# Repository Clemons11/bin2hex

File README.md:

# bin2hex
# Version 01 of the board

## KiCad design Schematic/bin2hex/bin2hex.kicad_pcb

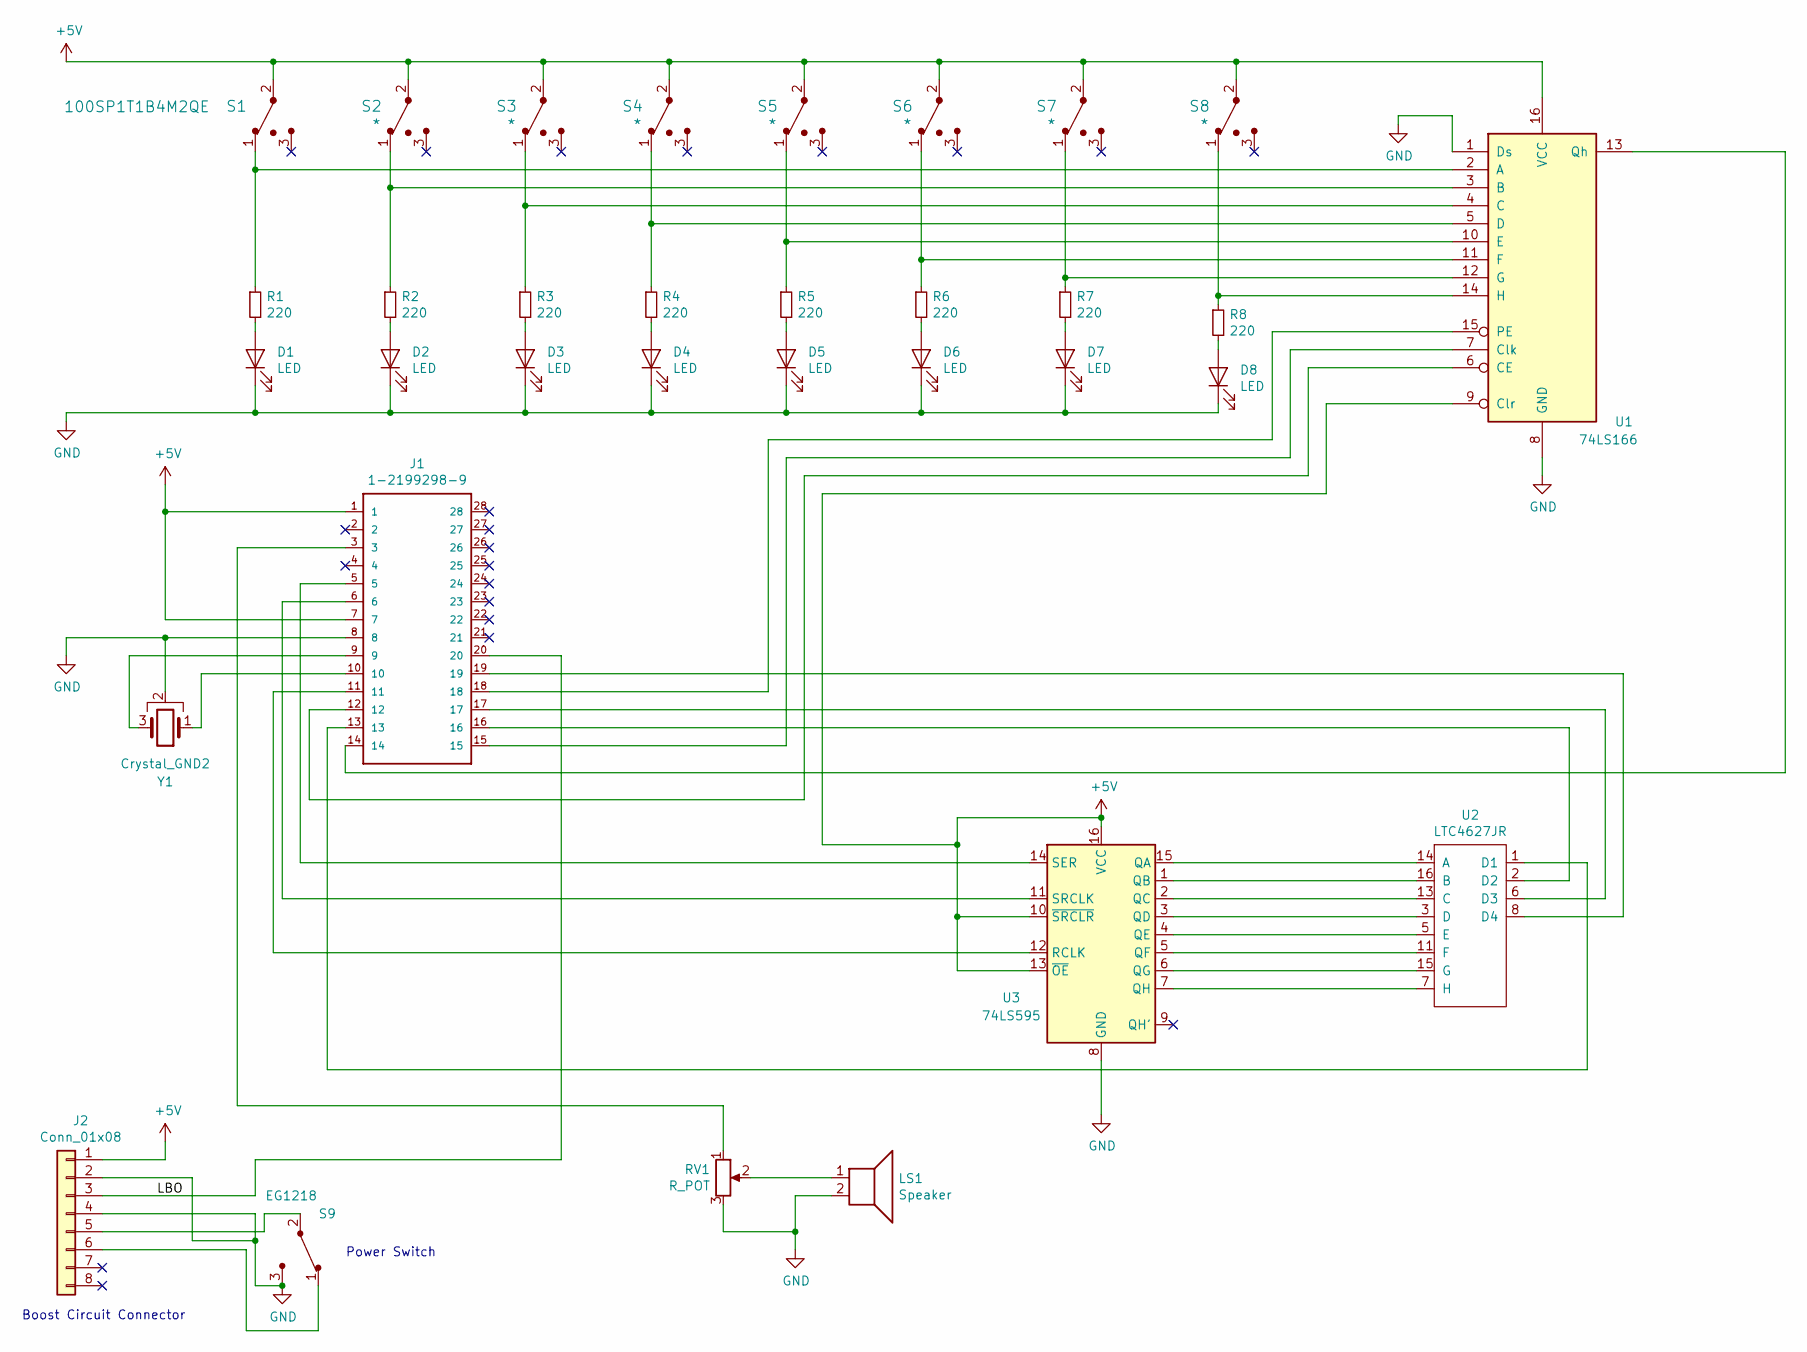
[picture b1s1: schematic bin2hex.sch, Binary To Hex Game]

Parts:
D1, D2, D3, D4, D5, D6, D7, D8: LED; TLUR4400
J1: 1-2199298-9; DIPS762W51P254L3550H419Q28N
J2: Conn_01x08; PinHeader_1x08_P2.54mm_Vertical
LS1: Speaker; SolderPad_1x2
R1, R2, R3, R4, R5, R6, R7, R8: 220; R_Axial_DIN0207_L6.3mm_D2.5mm_P7.62mm_Horizontal
RV1: R_POT; solderPads_1x3
S1: 100SP1T1B4M2QE; Toggle_Switch_100SP1T1B4M2QE; MPN 100SP1T1B4M2QE; Digi-Key_PN EG2355-ND
S2, S3, S4, S5, S6, S7, S8: *; Toggle_Switch_100SP1T1B4M2QE; MPN 100SP1T1B4M2QE; Digi-Key_PN EG2355-ND
S9: EG1218; Switch_Slide_11.6x4mm_EG1218; MPN EG1218; Digi-Key_PN EG1903-ND
U1: 74LS166; DIP254P762X508-16
U2: LTC4627JR
U3: 74LS595; DIP254P762X508-16
Y1: Crystal_GND2; XTAL_ZTT-16.00MX

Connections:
+5V: J1.1, J1.7, J2.1, S1.2 (Com), S2.2 (Com), S3.2 (Com), S4.2 (Com), S5.2 (Com), S6.2 (Com), S7.2 (Com), S8.2 (Com), U1.9 (Clr), U1.16 (VCC), U3.10 (~SRCLR), U3.13 (~OE), U3.16 (VCC)
/LBO: J1.20, J2.3
GND: D1.1 (K), D2.1 (K), D3.1 (K), D4.1 (K), D5.1 (K), D6.1 (K), D7.1 (K), D8.1 (K), J1.8, J2.2, J2.4, LS1.2, RV1.3, S9.3, U1.1 (Ds), U1.8 (GND), U3.8 (GND), Y1.2
unnamed: D1.2 (A), R1.2
unnamed: D2.2 (A), R2.2
unnamed: D3.2 (A), R3.2
unnamed: D4.2 (A), R4.2
unnamed: D5.2 (A), R5.2
unnamed: D6.2 (A), R6.2
unnamed: D7.2 (A), R7.2
unnamed: D8.2 (A), R8.2
unnamed: J1.3, RV1.1
unnamed: J1.5, U3.14 (SER)
unnamed: J1.6, U3.11 (SRCLK)
unnamed: J1.9, Y1.3
unnamed: J1.10, Y1.1
unnamed: J1.11, U3.12 (RCLK)
unnamed: J1.12, U1.6 (CE)
unnamed: J1.13, U2.1 (D1)
unnamed: J1.14, U1.13 (Qh)
unnamed: J1.15, U1.7 (Clk)
unnamed: J1.16, U2.2 (D2)
unnamed: J1.17, U2.6 (D3)
unnamed: J1.18, U1.15 (PE)
unnamed: J1.19, U2.8 (D4)
unnamed: J2.5, S9.2
unnamed: J2.6, S9.1
unnamed: LS1.1, RV1.2
unnamed: R1.1, S1.1, U1.2 (A)
unnamed: R2.1, S2.1, U1.3 (B)
unnamed: R3.1, S3.1, U1.4 (C)
unnamed: R4.1, S4.1, U1.5 (D)
unnamed: R5.1, S5.1, U1.10 (E)
unnamed: R6.1, S6.1, U1.11 (F)
unnamed: R7.1, S7.1, U1.12 (G)
unnamed: R8.1, S8.1, U1.14 (H)
unnamed: U2.3 (D), U3.3 (QD)
unnamed: U2.5 (E), U3.4 (QE)
unnamed: U2.7 (H), U3.7 (QH)
unnamed: U2.11 (F), U3.5 (QF)
unnamed: U2.13 (C), U3.2 (QC)
unnamed: U2.14 (A), U3.15 (QA)
unnamed: U2.15 (G), U3.6 (QG)
unnamed: U2.16 (B), U3.1 (QB)

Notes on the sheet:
Boost Circuit Connector
Power Switch

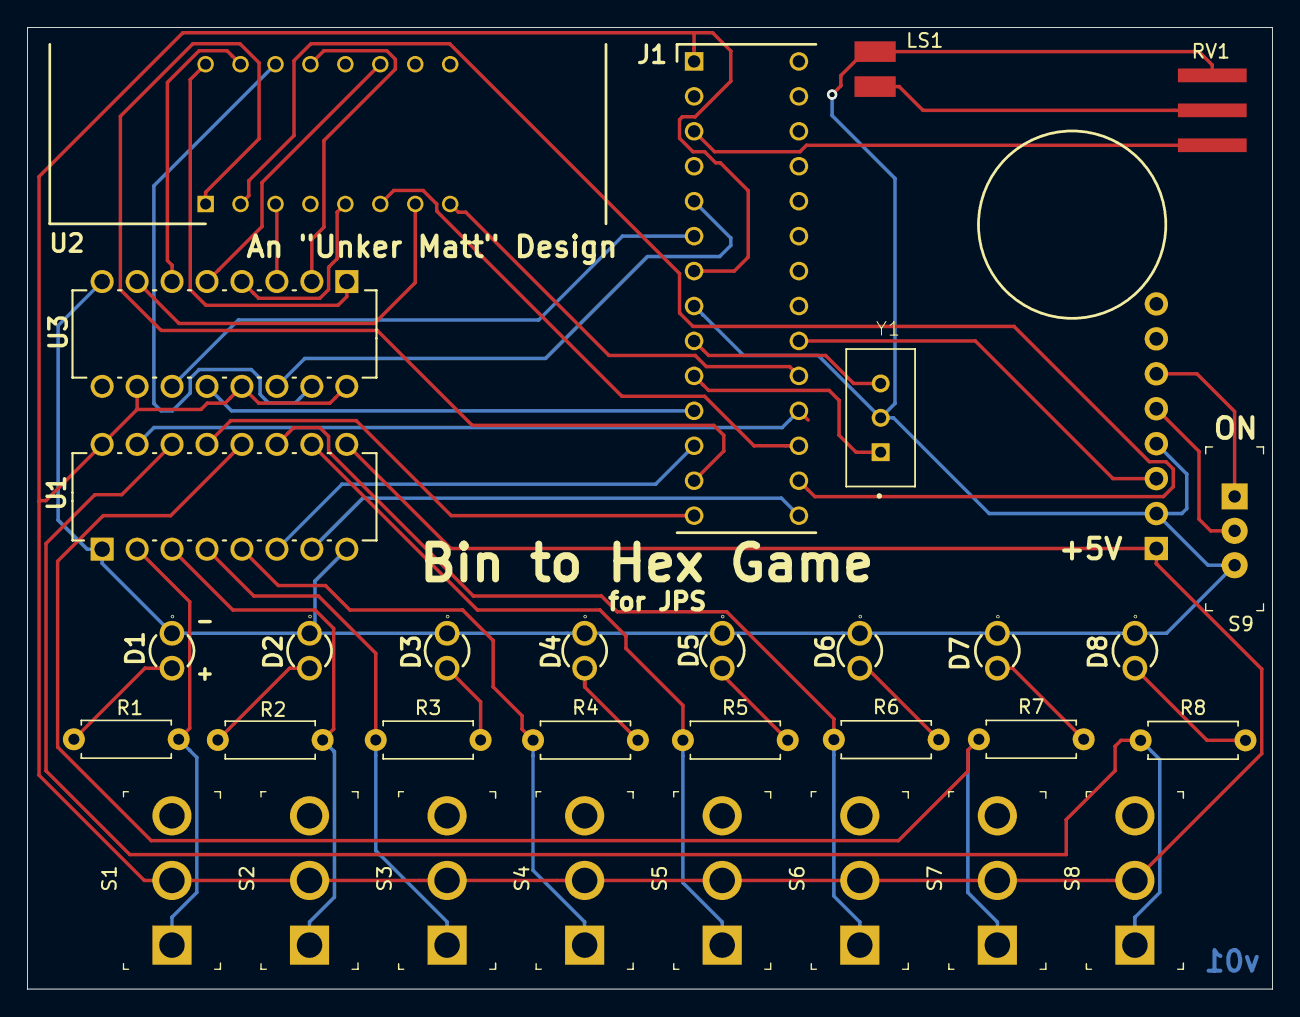
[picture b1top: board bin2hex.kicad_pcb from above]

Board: 2 copper layers, 90.5 x 69.9 mm, 33 parts (1 on the bottom side), 44 nets.

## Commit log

2019-11-05 Updated readme to match board version
